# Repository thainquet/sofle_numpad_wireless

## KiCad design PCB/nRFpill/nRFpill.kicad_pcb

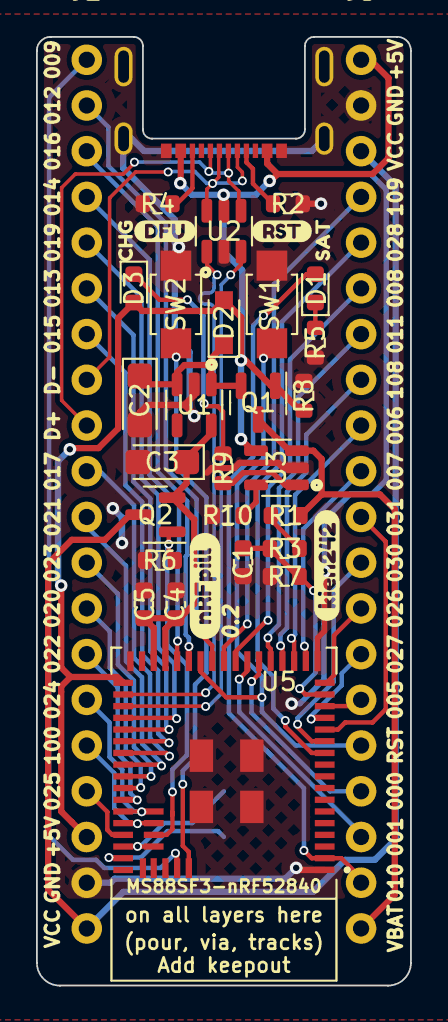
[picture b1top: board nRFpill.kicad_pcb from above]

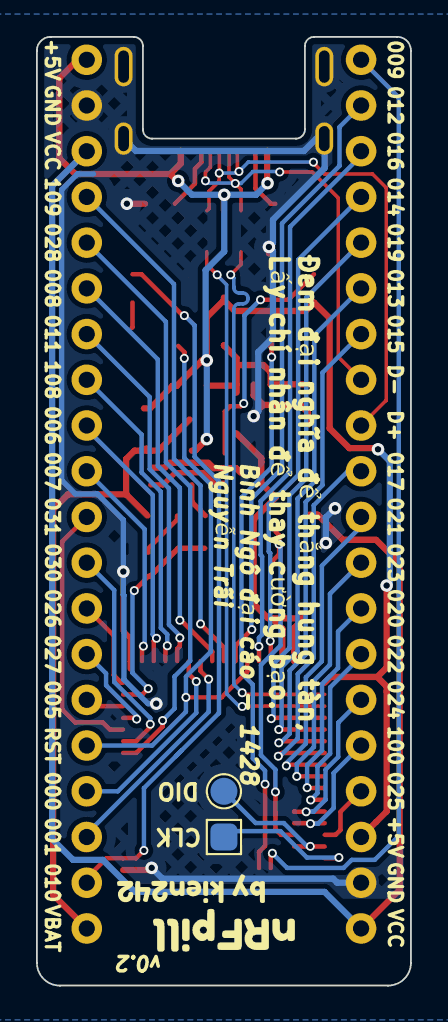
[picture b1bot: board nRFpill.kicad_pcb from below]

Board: 2 copper layers, 20.8 x 52.7 mm, 39 parts (4 on the bottom side), 53 nets.

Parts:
C1, C5: 100nF; C_0603_1608Metric
C2, C3: 10uF; CP_EIA-3216-12_Kemet-S
C4: 10uF; C_0603_1608Metric
D1, D3: BLUE; LED_0603_1608Metric
D2: 1N5819; D_SOD-323_HandSoldering
J1: USB_C_Receptacle_USB2.0; USB-C-Low
J2, J3: PinHeader_1x20_P2.54mm_Vertical
J4: TestPoint_Pad_1.5x1.5mm
J5: TestPoint_Pad_D1.5mm
Q1, Q2: AO3407; SOT-23
R1, R3: 2M; R_0603_1608Metric
R2, R4: 5.1k; R_0603_1608Metric
R5, R9: 1K; R_0603_1608Metric
R6: 100k; R_0603_1608Metric
R7: 10M; R_0603_1608Metric
R8: 100K; R_0603_1608Metric
R10: 2.3k; R_0603_1608Metric
SW1: RST; SW_SPST_B3U-1000P
SW2: DFU; SW_SPST_B3U-1000P
U1: MIC5219-3.3YM5; SOT-23-5
U2: USBLC6-2SC6; SOT-23-6
U3: TP4054; SOT-23-5
U5: MS88FS3; MODULE_MS88SF3
kibuzzard-62FEE3AB: G***; kibuzzard-62FEE3AB
kibuzzard-62FEE358: G***; kibuzzard-62FEE358
kibuzzard-6303CF12: G***; kibuzzard-6303CF12
kibuzzard-6303CF50: G***; kibuzzard-6303CF50
kibuzzard-6303CFD4: G***; kibuzzard-6303CFD4
kibuzzard-6303D094: G***; kibuzzard-6303D094
kibuzzard-63049CD9: G***; kibuzzard-63049CD9
kibuzzard-63049CF8: G***; kibuzzard-63049CF8

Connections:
0.00: J3.17, U5.23 (0.00)
0.01: J3.18, U5.24 (0.01)
0.05: J3.15, U5.15 (0.05*/AIN3)
0.06: J3.9, U5.20 (0.06*)
0.07: J3.10, U5.19 (0.07*)
0.08: J3.6, U5.25 (0.08*)
0.11: J3.7, U5.22 (0.11*)
0.12: J2.2, U5.27 (0.12*)
0.13: J2.6, U5.39 (*0.13)
0.14: J2.4, U5.30 (0.14*)
0.15: J2.7, U5.40 (*0.15)
0.16: J2.3, U5.29 (0.16*)
0.17: J2.10, U5.41 (*0.17)
0.19: J2.5, U5.38 (*0.19)
0.20: J2.13, U5.44 (*0.20)
0.21: J2.11, U5.42 (*0.21)
0.22: J2.14, U5.45 (*0.22)
0.23: J2.12, U5.43 (*0.23)
0.24: J2.15, U5.46 (*0.24), U5.60 (1.03)
0.25: J2.17, U5.48 (*0.25)
0.26: J3.13, U5.17 (0.26*)
0.27: J3.14, U5.14 (0.27*)
0.28: J3.5, U5.11 (0.28/AIN4)
0.30: J3.12, U5.12 (0.30/AIN6)
0.31: J3.11, U5.13 (0.31/AIN7)
1.00: J2.16, U5.47 (*1.00), U5.59 (1.01)
1.08: J3.8, U5.21 (1.08*)
1.09: J3.4, U5.26 (1.09*)
009: J2.1, U5.55 (0.09)
+5V: D2.2 (A), D3.2 (A), J1.A4 (VBUS), J1.A9 (VBUS), J1.B4 (VBUS), J1.B9 (VBUS), J2.18, J3.1, Q1.1 (G), R8.1, U2.5 (VBUS), U3.4 (VDD), U5.35 (VBUS)
BATTERY_PIN: C1.1, R3.2, R7.1, U5.16 (0.04*/AIN2)
D+: U2.3 (I/O2), U5.37 (D+)
D-: U2.1 (I/O1), U5.36 (D-)
DFU: SW2.2, U5.56 (0.10)
DP+: J1.A6 (D+), J1.B6 (D+), J2.9, U2.4 (I/O2)
DP-: J1.A7 (D-), J1.B7 (D-), J2.8, U2.6 (I/O1)
GND: C1.2, C2.2, C3.2, C4.2, C5.2, J1.A1 (GND), J1.A12 (GND), J1.B1 (GND), J1.B12 (GND), J1.S1 (SHIELD), J2.19, J3.2, R2.2, R4.1, R5.1, R6.2, R7.2, R8.2, R10.2, SW1.1, SW2.1, U1.2 (GND), U2.2 (GND), U3.2 (VSS), U5.1 (GND), U5.18 (GND), U5.34 (GND), U5.61, U5.62, U5.63, U5.64
LED_1: D1.2 (A), J3.19, U5.2 (1.11)
unnamed: C2.1, D2.1 (K), Q1.2 (S), U1.1 (IN), U1.3 (EN)
unnamed: D1.1 (K), R5.2
unnamed: D3.1 (K), R9.1
unnamed: J1.A5 (CC1), R2.1
unnamed: J1.B5 (CC2), R4.2
unnamed: R1.2, R3.1
unnamed: R9.2, U3.1 (STAT)
unnamed: R10.1, U3.5 (PROG)
POWER_PIN: Q2.1 (G), R6.1, U5.58 (1.05)
RST: J3.16, SW1.2, U5.28 (0.18/RESET)
SWCLK: J4.1, U5.50 (SWCLK)
SWDIO: J5.1, U5.49 (SWDIO), U5.57 (1.07)
VBAT: J3.20, Q1.3 (D), R1.1, U3.3 (VBAT)
VCC: J2.20, J3.3, Q2.3 (D)
nRF_VDD: C3.1, C4.1, C5.1, Q2.2 (S), U1.5 (OUT), U5.31 (VDD), U5.32 (VDDH)

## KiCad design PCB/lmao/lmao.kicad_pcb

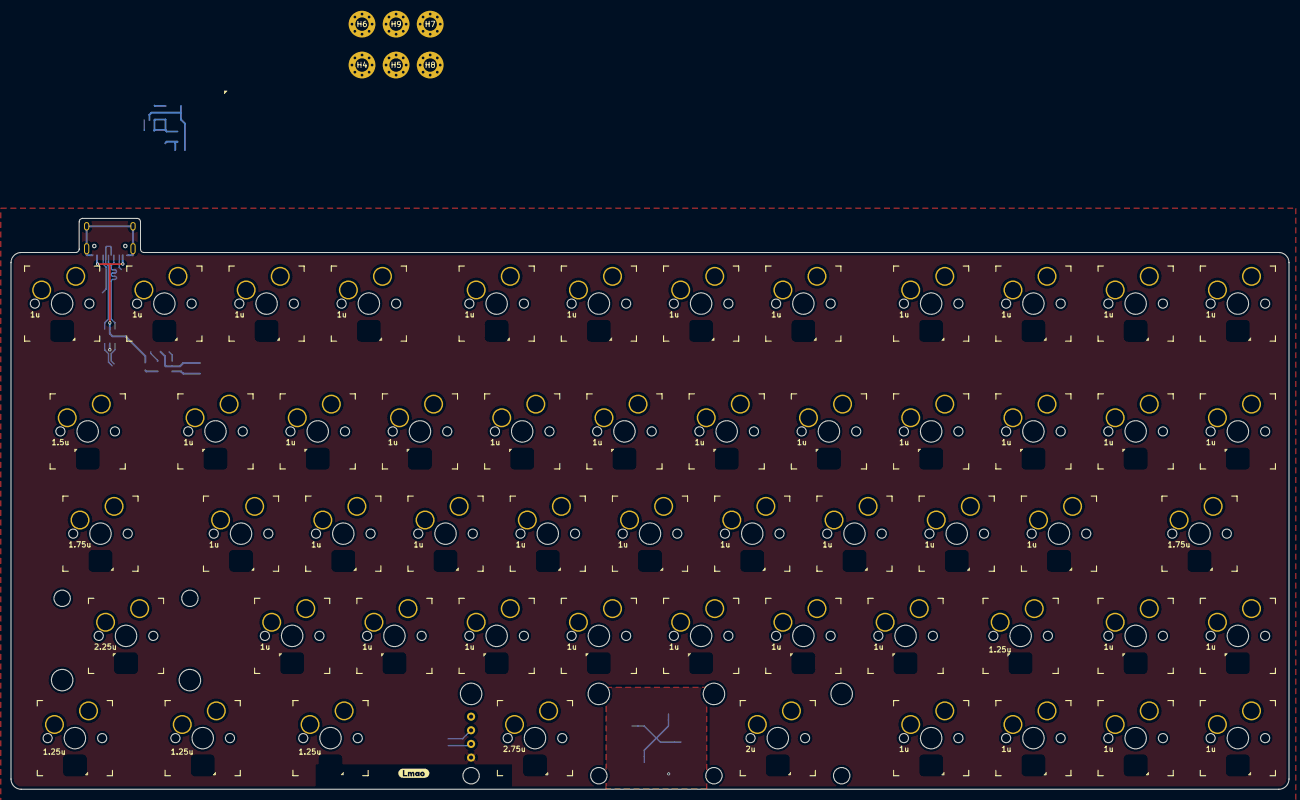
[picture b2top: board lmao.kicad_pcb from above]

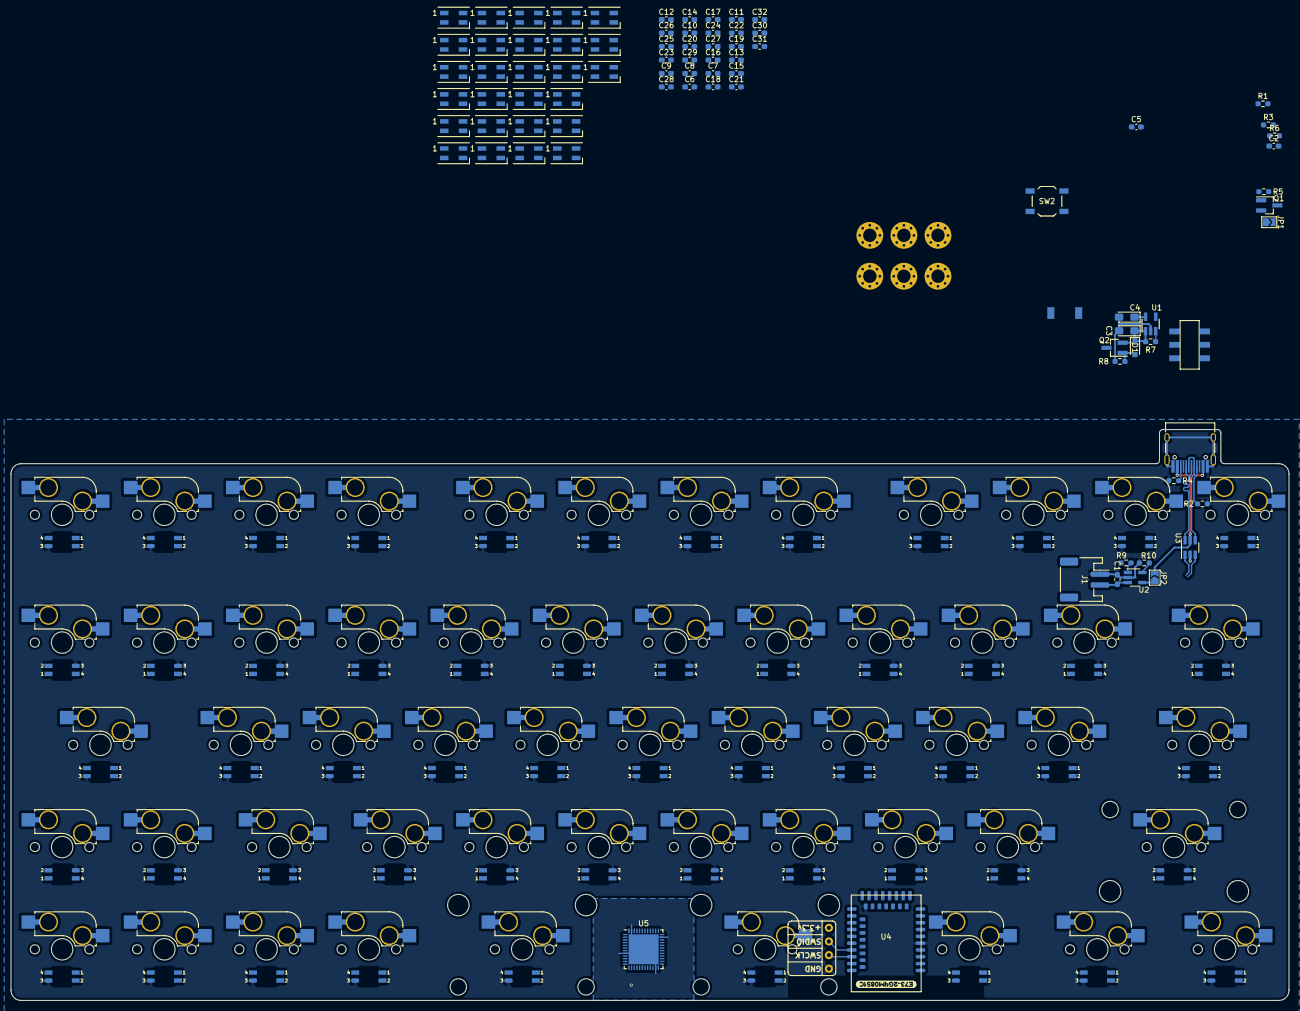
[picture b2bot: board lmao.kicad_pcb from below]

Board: 2 copper layers, 238.1 x 106.4 mm, 205 parts (84 on the bottom side), 105 nets.

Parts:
C1: 10nF; C_0603_1608Metric_Pad1.08x0.95mm_HandSolder
C2: 1nF; C_0603_1608Metric_Pad1.08x0.95mm_HandSolder
C3, C4: 10uF; CP_EIA-3216-12_Kemet-S_Pad1.58x1.35mm_HandSolder
C5: 10uF; C_0603_1608Metric_Pad1.08x0.95mm_HandSolder
C6, C7, C8, C9, C10, C11, C12, C13, C14, C15, C16, C17, C18, C19, C20, C21, C22, C23, C24, C25, C26, C27, C28, C29, C30, C31, C32: C; C_0603_1608Metric_Pad1.08x0.95mm_HandSolder
D1: 1N5819; D_SOD-323_HandSoldering
D2: BLUE; LED6028-3228-2pin
H1, H2, H3: Stab
H4, H5, H6, H7, H8, H9: Hole; MountingHole_2.5mm_Pad_Via
J1: JST_PH_S2B-PH-SM4-TB_1x02-1MP_P2.00mm_Horizontal
J2: USB_C_Receptacle_USB2.0; USB-C-16pin-hight-v2
JP1, JP2: SolderJumper-2_P1.3mm_Open_TrianglePad1.0x1.5mm
LED1, LED2, LED3, LED4, LED5, LED6, LED7, LED8, LED9, LED10, LED11, LED12, LED13, LED14, LED15, LED16, LED17, LED18, LED19, LED20, LED21, LED22, LED23, LED24, LED25, LED26, LED27: 6812; SK6812-MINI
LED28, LED29, LED30, LED31, LED32, LED33, LED34, LED35, LED36, LED37, LED38, LED39, LED40, LED41, LED42, LED43, LED44, LED45, LED46, LED47, LED48, LED49, LED50, LED51, LED52, LED53, LED54, LED55, LED56, LED57, LED58, LED59, LED60, LED61, LED62, LED63, LED64, LED65, LED66, LED67, LED68, LED69, LED70, LED71, LED72, LED73, LED74, LED75, LED76, LED77, LED78, LED79, LED80, LED81, LED82: SK6812Mini-E
Q1, Q2: AO3407; SOT-23_Handsoldering
R1, R3: 2m; R_0603_1608Metric_Pad0.98x0.95mm_HandSolder
R2, R4: 5.1k; R_0603_1608Metric_Pad0.98x0.95mm_HandSolder
R5: 2M; R_0603_1608Metric_Pad0.98x0.95mm_HandSolder
R6: 10M; R_0603_1608Metric_Pad0.98x0.95mm_HandSolder
R7, R8: 100K; R_0603_1608Metric_Pad0.98x0.95mm_HandSolder
R9: 1K; R_0603_1608Metric_Pad0.98x0.95mm_HandSolder
R10: RPROG; R_0603_1608Metric_Pad0.98x0.95mm_HandSolder
SW1: MSS22D18
SW2: SW_Push; SW_SPST_TL3342
SW3, SW4, SW5, SW6, SW7, SW8, SW9, SW10, SW11, SW12, SW13, SW14, SW16, SW17, SW18, SW19, SW20, SW21, SW22, SW23, SW24, SW25, SW26, SW28, SW29, SW30, SW31, SW32, SW33, SW34, SW35, SW36, SW39, SW40, SW41, SW42, SW43, SW44, SW45, SW47, SW48, SW54, SW55, SW56, SW57: 1u; SW-HS-1u
SW15: 1.5u; SW-HS-1.5u
SW27, SW37: 1.75u; SW-HS-1.75u
SW38: 2.25u; SW-HS-2.25u
SW46, SW49, SW50, SW51: 1.25u; SW-HS-1.25u
SW52: 2.75u; SW-HS-2.75u
SW53: 2u; SW-HS-2u
SWD1: SWD-4Pin
U1: MIC5219-3.3YM5; SOT-23-5_HandSoldering
U2: TP4054; SOT-23-5_HandSoldering
U3: USBLC6-2SC6; SOT-23-6_Handsoldering
U4: E73-2G4M08S1C
U5: STM32F401CBUx; QFN-48-1EP_7x7mm_P0.5mm_EP5.6x5.6mm
kibuzzard-62F0EFF6: G***; kibuzzard-62F0EFF6

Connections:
+5V: D1.2 (A), LED28.+, LED29.+, LED30.+, LED31.+, LED32.+, LED33.+, LED34.+, LED35.+, LED36.+, LED37.+, LED38.+, LED39.+, LED40.+, LED41.+, LED42.+, LED43.+, LED44.+, LED45.+, LED46.+, LED47.+, LED48.+, LED49.+, LED50.+, LED51.+, LED52.+, LED53.+, LED54.+, LED55.+, LED56.+, LED57.+, LED58.+, LED59.+, LED60.+, LED61.+, LED62.+, LED63.+, LED64.+, LED65.+, LED66.+, LED67.+, LED68.+, LED69.+, LED70.+, LED71.+, LED72.+, LED73.+, LED74.+, LED75.+, LED76.+, LED77.+, LED78.+, LED79.+, LED80.+, LED81.+, LED82.+, Q2.1 (G), R8.1
BATTERY_PIN: C2.1, R3.2, R6.1
BAT_CTR: R7.2, SW1.3 (C), U1.3 (CE)
D+: U3.1 (I/O1), U4.31 (D+)
D-: U3.3 (I/O2), U4.29 (D-)
DP+: J2.A6 (D+), J2.B6 (D+), U3.6 (I/O1)
DP-: J2.A7 (D-), J2.B7 (D-), U3.4 (I/O2)
GND: C1.2, C2.2, C3.2, C4.2, C5.2, C6.2, C7.2, C8.2, C9.2, C10.2, C11.2, C12.2, C13.2, C14.2, C15.2, C16.2, C17.2, C18.2, C19.2, C20.2, C21.2, C22.2, C23.2, C24.2, C25.2, C26.2, C27.2, C28.2, C29.2, C30.2, C31.2, C32.2, J1.1, J2.A1 (GND), J2.A12 (GND), J2.B1 (GND), J2.B12 (GND), J2.S1 (SHIELD), LED1.-, LED2.-, LED3.-, LED4.-, LED5.-, LED6.-, LED7.-, LED8.-, LED9.-, LED10.-, LED11.-, LED12.-, LED13.-, LED14.-, LED15.-, LED16.-, LED17.-, LED18.-, LED19.-, LED20.-, LED21.-, LED22.-, LED23.-, LED24.-, LED25.-, LED26.-, LED27.-, LED28.-, LED29.-, LED30.-, LED31.-, LED32.-, LED33.-, LED34.-, LED35.-, LED36.-, LED37.-, LED38.-, LED39.-, LED40.-, LED41.-, LED42.-, LED43.-, LED44.-, LED45.-, LED46.-, LED47.-, LED48.-, LED49.-, LED50.-, LED51.-, LED52.-, LED53.-, LED54.-, LED55.-, LED56.-, LED57.-, LED58.-, LED59.-, LED60.-, LED61.-, LED62.-, LED63.-, LED64.-, LED65.-, LED66.-, LED67.-, LED68.-, LED69.-, LED70.-, LED71.-, LED72.-, LED73.-, LED74.-, LED75.-, LED76.-, LED77.-, LED78.-, LED79.-, LED80.-, LED81.-, LED82.-, R2.2, R4.1, R5.2, R6.2, R8.2, R10.2, SW1.2 (B), SW2.1, SWD1.1 (GND), U1.2 (GND), U2.2 (VSS), U3.2 (GND), U4.5 (GND), U4.21 (GND), U4.24 (GND)
GND1: U5.8 (VSSA), U5.23 (VSS), U5.35 (VSS), U5.47 (VSS), U5.49 (VSS)
unnamed: C3.1, D1.1 (K), Q2.2 (S), R7.1, U1.1 (VIN)
unnamed: D2.1 (K), R9.1
unnamed: D2.2 (A), JP2.1 (A), U2.4 (VDD)
unnamed: J2.A5 (CC1), R2.1
unnamed: J2.B5 (CC2), R4.2
unnamed: LED1.O (OUT), LED2.I (IN)
unnamed: LED2.O (OUT), LED3.I (IN)
unnamed: LED3.O (OUT), LED4.I (IN)
unnamed: LED4.O (OUT), LED5.I (IN)
unnamed: LED5.O (OUT), LED6.I (IN)
unnamed: LED6.O (OUT), LED7.I (IN)
unnamed: LED7.O (OUT), LED8.I (IN)
unnamed: LED8.O (OUT), LED9.I (IN)
unnamed: LED10.I (IN), LED11.O (OUT)
unnamed: LED10.O (OUT), LED19.I (IN)
unnamed: LED11.I (IN), LED12.O (OUT)
unnamed: LED12.I (IN), LED13.O (OUT)
unnamed: LED13.I (IN), LED14.O (OUT)
unnamed: LED14.I (IN), LED15.O (OUT)
unnamed: LED15.I (IN), LED16.O (OUT)
unnamed: LED16.I (IN), LED17.O (OUT)
unnamed: LED17.I (IN), LED18.O (OUT)
unnamed: LED9.O (OUT), LED18.I (IN)
unnamed: LED19.O (OUT), LED20.I (IN)
unnamed: LED20.O (OUT), LED21.I (IN)
unnamed: LED21.O (OUT), LED22.I (IN)
unnamed: LED22.O (OUT), LED23.I (IN)
unnamed: LED23.O (OUT), LED24.I (IN)
unnamed: LED24.O (OUT), LED25.I (IN)
unnamed: LED25.O (OUT), LED26.I (IN)
unnamed: LED26.O (OUT), LED27.I (IN)
unnamed: LED28.O (OUT), LED29.I (IN)
unnamed: LED29.O (OUT), LED30.I (IN)
unnamed: LED30.O (OUT), LED31.I (IN)
unnamed: LED31.O (OUT), LED32.I (IN)
unnamed: LED32.O (OUT), LED33.I (IN)
unnamed: LED33.O (OUT), LED34.I (IN)
unnamed: LED34.O (OUT), LED35.I (IN)
unnamed: LED35.O (OUT), LED36.I (IN)
unnamed: LED36.O (OUT), LED37.I (IN)
unnamed: LED37.O (OUT), LED38.I (IN)
unnamed: LED38.O (OUT), LED39.I (IN)
unnamed: LED39.O (OUT), LED40.I (IN)
unnamed: LED40.O (OUT), LED41.I (IN)
unnamed: LED41.O (OUT), LED42.I (IN)
unnamed: LED42.O (OUT), LED43.I (IN)
unnamed: LED43.O (OUT), LED44.I (IN)
unnamed: LED44.O (OUT), LED45.I (IN)
unnamed: LED45.O (OUT), LED46.I (IN)
unnamed: LED46.O (OUT), LED47.I (IN)
unnamed: LED47.O (OUT), LED48.I (IN)
unnamed: LED48.O (OUT), LED49.I (IN)
unnamed: LED49.O (OUT), LED50.I (IN)
unnamed: LED50.O (OUT), LED51.I (IN)
unnamed: LED51.O (OUT), LED52.I (IN)
unnamed: LED52.O (OUT), LED53.I (IN)
unnamed: LED53.O (OUT), LED54.I (IN)
unnamed: LED54.O (OUT), LED55.I (IN)
unnamed: LED55.O (OUT), LED56.I (IN)
unnamed: LED56.O (OUT), LED57.I (IN)
unnamed: LED57.O (OUT), LED58.I (IN)
unnamed: LED58.O (OUT), LED59.I (IN)
unnamed: LED59.O (OUT), LED60.I (IN)
unnamed: LED60.O (OUT), LED61.I (IN)
unnamed: LED61.O (OUT), LED62.I (IN)
unnamed: LED62.O (OUT), LED63.I (IN)
unnamed: LED63.O (OUT), LED64.I (IN)
unnamed: LED64.O (OUT), LED65.I (IN)
unnamed: LED65.O (OUT), LED66.I (IN)
unnamed: LED66.O (OUT), LED67.I (IN)
unnamed: LED67.O (OUT), LED68.I (IN)
unnamed: LED68.O (OUT), LED69.I (IN)
unnamed: LED69.O (OUT), LED70.I (IN)
unnamed: LED70.O (OUT), LED71.I (IN)
unnamed: LED71.O (OUT), LED72.I (IN)
unnamed: LED72.O (OUT), LED73.I (IN)
unnamed: LED73.O (OUT), LED74.I (IN)
unnamed: LED74.O (OUT), LED75.I (IN)
unnamed: LED75.O (OUT), LED76.I (IN)
unnamed: LED76.O (OUT), LED77.I (IN)
unnamed: LED77.O (OUT), LED78.I (IN)
unnamed: LED78.O (OUT), LED79.I (IN)
unnamed: LED79.O (OUT), LED80.I (IN)
unnamed: LED80.O (OUT), LED81.I (IN)
unnamed: LED81.O (OUT), LED82.I (IN)
unnamed: R1.2, R3.1
unnamed: R9.2, U2.1 (STAT)
unnamed: R10.1, U2.5 (PROG)
POWER_PIN: Q1.1 (G), R5.1
RST: SW2.2, U4.26 (P0.18/RESET)
SWCLK: SWD1.2 (CLK), U4.39 (SWDCLK)
SWDIO: SWD1.3 (DIO), U4.37 (SWDIO)
VBAT: C1.1, J1.2, Q2.3 (D), R1.1, U2.3 (VBAT)
VBUS: J2.A4 (VBUS), J2.A9 (VBUS), J2.B4 (VBUS), J2.B9 (VBUS), JP2.2 (B), U3.5 (VBUS), U4.27 (VBUS)
VCC: C6.1, C7.1, C8.1, C9.1, C10.1, C11.1, C12.1, C13.1, C14.1, C15.1, C16.1, C17.1, C18.1, C19.1, C20.1, C21.1, C22.1, C23.1, C24.1, C25.1, C26.1, C27.1, C28.1, C29.1, C30.1, C31.1, C32.1, JP1.2 (B), LED1.+, LED2.+, LED3.+, LED4.+, LED5.+, LED6.+, LED7.+, LED8.+, LED9.+, LED10.+, LED11.+, LED12.+, LED13.+, LED14.+, LED15.+, LED16.+, LED17.+, LED18.+, LED19.+, LED20.+, LED21.+, LED22.+, LED23.+, LED24.+, LED25.+, LED26.+, LED27.+, Q1.3 (D)
VDD: C4.1, C5.1, JP1.1 (A), Q1.2 (S), SWD1.4 (3.3V), U1.5 (VOUT), U4.19 (VDD), U4.23 (VDDH)

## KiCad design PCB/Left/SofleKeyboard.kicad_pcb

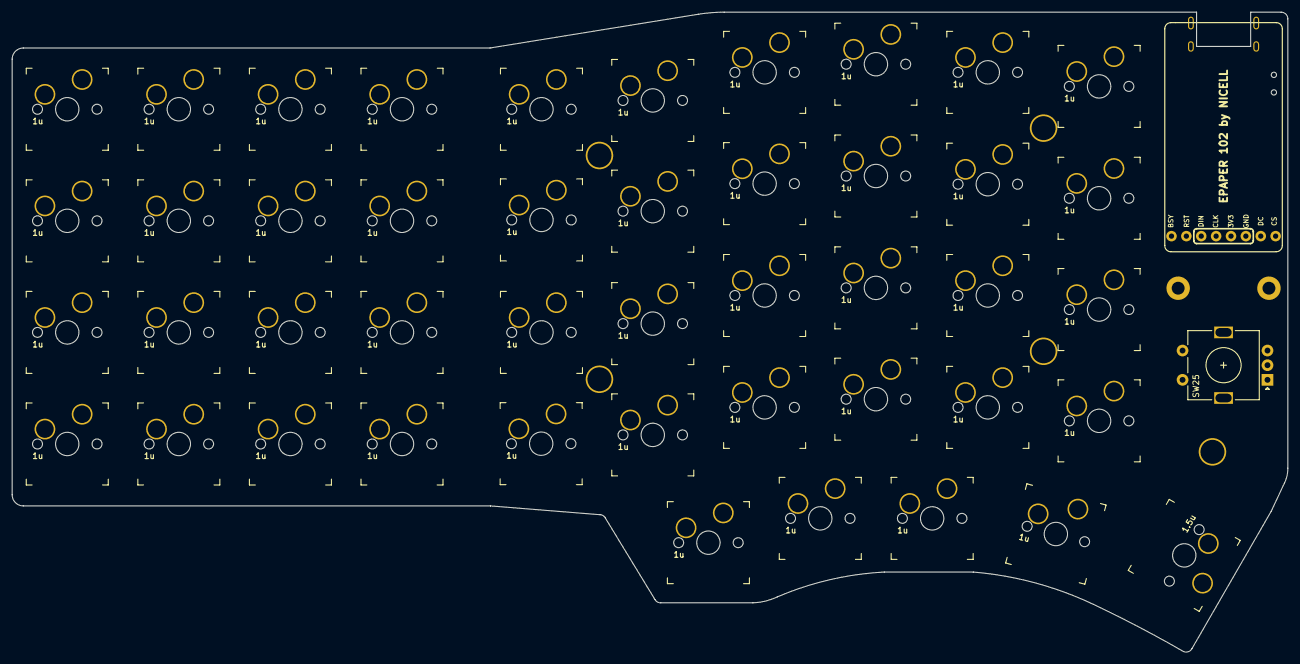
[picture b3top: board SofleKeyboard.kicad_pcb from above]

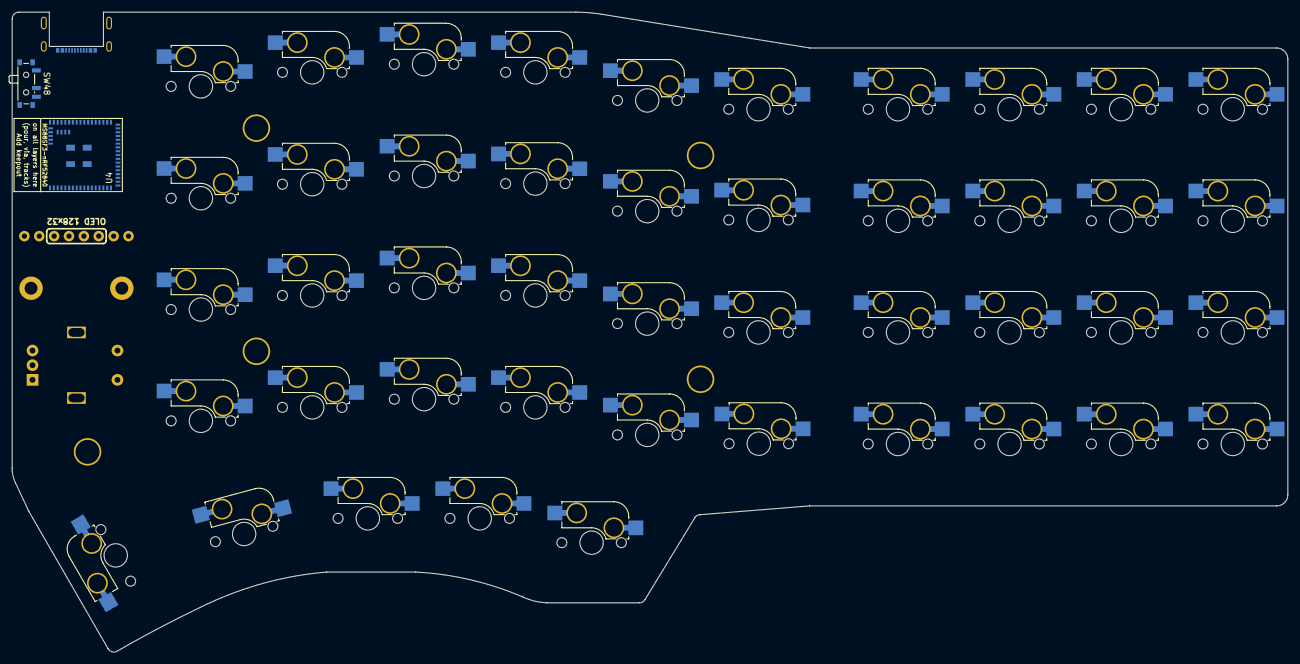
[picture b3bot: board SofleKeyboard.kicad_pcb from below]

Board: 2 copper layers, 217.8 x 109.2 mm, 57 parts (3 on the bottom side), 15 nets, no tracks yet.

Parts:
J1: Conn_01x08; epaper-102
J2: USB-C-Low
SW1, SW2, SW3, SW4, SW5, SW6, SW7, SW8, SW9, SW10, SW11, SW12, SW13, SW14, SW15, SW16, SW17, SW18, SW19, SW20, SW21, SW22, SW23, SW24, SW27, SW28, SW29, SW30, SW31, SW32, SW33, SW34, SW35, SW36, SW37, SW38, SW39, SW40, SW41, SW42, SW43, SW44, SW45, SW46: 1u; SW-HS-1u
SW25: Rotary_Encoder_Switch; RotaryEncoder_Alps_EC11E-Switch_Vertical_H20mm
SW26: 1.5u; SW-HS-1.5u
SW48: Power Switch; SW_SPDT_PCM12
TH1, TH2: HOLE; M2_HOLE_PCB
TH3, TH4, TH5, TH6, TH7: HOLE; HOLE_M2_TH
U4: MS88FS3; MS88SF3-nRF52840

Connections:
DP+: J2.A6 (D+), J2.B6 (D+)
DP-: J2.A7 (D-), J2.B7 (D-)
GND: J1.3, J2.A1 (GND), J2.A12 (GND), J2.B1 (GND), J2.B12 (GND), J2.S1 (SHIELD), SW25.C, U4.1 (GND), U4.18 (GND), U4.61
unnamed: SW31.1, SW35.1, SW39.1, SW43.1
unnamed: SW32.1, SW36.1, SW40.1, SW44.1
unnamed: SW33.1, SW37.1, SW41.1, SW45.1
unnamed: SW34.1, SW38.1, SW42.1, SW46.1
SW25A: SW1.1, SW7.1, SW13.1, SW19.1, SW25.S1
VBUS: J2.A4 (VBUS), J2.A9 (VBUS), J2.B4 (VBUS), J2.B9 (VBUS), U4.35 (VBUS)
col0: SW6.1, SW12.1, SW18.1, SW24.1, SW30.1
col1: SW5.1, SW11.1, SW17.1, SW23.1, SW29.1
col2: SW4.1, SW10.1, SW16.1, SW22.1, SW28.1
col3: SW3.1, SW9.1, SW15.1, SW21.1, SW27.1
col4: SW2.1, SW8.1, SW14.1, SW20.1, SW26.1
nRF_VDD: U4.31 (VDD), U4.32 (VDDH)

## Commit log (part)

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2022-06-07 fist
2022-06-08 cập nhật 12:21 08/06/2022
2022-06-08 cap nhat 16:16 08/06/2022
2022-06-12 Cap nhat 18:33 12/06/2022
2022-06-12 cap nhat luc nua dem 23:54 12/06/2022
2022-06-13 cap nhat 11:55 13/06/2022
2022-06-13 18:29 13/06/2022
2022-06-18 Cập nhật 22:10 18/06/2022
2022-06-18 22:41 18/06/2022
2022-08-05 Update PCB
2022-08-05 cap nhat
2022-08-06 Add lmao keyboard
2022-08-07 Update Lmao
2022-08-07 Cập nhật Lmao
2022-08-12 update Lmao keyboard
2022-08-22 update file
2022-08-22 Cập nhật nRFpill: - Cần tạo PCB mới, thay thế cho v0.1 chưa kết nối ext-power
2022-08-22 update build
2022-08-22 add setting_reset
2022-08-23 aaaa
2022-08-25 cập nhật
2022-08-25 cap nhat lại
2022-08-25 cập nhật 2
2022-08-25 cập nhật tên
2022-08-25 cập nhật build.yaml
2022-08-25 gggg
2022-08-25 âdfafd
2022-08-25 adfaffa
2022-08-25 adfa
2022-08-25 adfaf
2022-08-25 ầdfaf
2022-08-25 aaaaaaa
2022-08-25 aaaaa
2022-08-25 asdf
2022-08-25 afadfa faf
2022-08-25 cap nhạt
2022-08-25 aaaaaa
2022-08-26 cập nhật bên right
2022-08-26 cập nhật right
2022-08-26 vvvv
2022-08-26 fix1
2022-08-26 fix right 2
2022-08-26 fix left 0
2022-08-27 fix left 2
2022-08-27 fix right encoder 1
2022-08-27 update keymap
2022-08-27 fix left 1
2022-08-27 fix left 3
2022-08-27 fix col 4 left
2022-08-27 fix left col 7
2022-08-27 fix left 5
2022-08-30 cap nhat PCB
2022-09-05 enable RGB
2022-09-05 ffff
2022-09-05 update left
2022-09-05 update right
2022-09-05 hsdfh
2022-09-05 1111
2022-09-05 left í mmasster
2022-09-05 capnhat
